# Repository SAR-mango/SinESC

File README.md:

# Current State of the Project
I graduated from UCSB in June 2026, and SinESC has been revived!

After studying electrical engineering for four years, I have realized that the true problem to solve – and the key to SinESC's success – is developing a sensorless FOC algorithm that operates reliably, without manual tuning, across a wide range of motors.

Accordingly, I have shifted away from ST's motor control library in favor of my own software, developed from scratch. For now, I am using evaluation boards to perform testing. Building robust, high-performance hardware is a secondary focus, since this has already been done by others. Nevertheless, I plan to eventually revamp the hardware.

# Overview
SinESC (pronounced "sign ESC," namesake being the sine wave) is an electronic speed controller (ESC) that supports sensorless field-oriented control of three-phase brushless DC motors used by RC drone pilots. For a brief overview of the project and the underlying theory, see [these slides](https://github.com/SAR-mango/SinESC/blob/master/sinesc_slides/sinesc_slides.pdf) – adapted from a presentation I gave at SpaceX for an onsite interview.

The dimensions of the PCBs pictured below are 15x30mm.

# Features, Specifications*
- 90% efficiency (up to 40% longer flight)
- Smooth flight
- Quiet operation
- Bus voltage monitoring for power measurement and under-voltage protection
- Broken-out and labeled debug pins
- 3–6S Li-po battery support
- Maximum 30A continuous, 40A burst current draw

\*Several of the above specifications are currently only theoretical; they have not been confirmed with measurements. This page will be updated immediately when any specification changes or is confirmed.

# Sinusoidal Control: Benefits and a Brief Description
Brushless DC motors work best when their phase voltage waveforms are sinusoid-shaped. Try it yourself—connect a BLDC motor to an oscilloscope and spin the rotor with your fingers. You will see a sine wave. 

Regular BLHELI_32 ESCs use a simple "six-point" motor control method in which the phases are energized to bring the rotor to one of six points on a circle. This method is easy to implement as the rotor position at each point will result in a zero-crossing in the back-EMF from the non-energized phase(s), which is easy to detect. This means that the phase voltage waveforms are trapezoid-shaped rather than sinusoid-shaped. This is not ideal as the fields are not *always* aligned with the rotor to maximize torque. This causes the rotor to effectively "jolt in a circle" rather than spin continuously, resulting in lower efficiency and rougher flight. Furthermore, the sharp edges of the trapezoidal signal also introduce high-frequency noise which contributes to the above disadvantages as well. This also makes the motors run louder and hotter.

Sinusoidal control minimizes torque ripple, maximizing efficiency. The magnetic fields are precisely aligned to exert maximum torque on the rotor at *any* given position and power. Minimized torque ripple leads to smoother flight. Greater efficiency (SinESC achieves > 90% efficiency; trapezoidal ESCs typically achieve around 70%) allows for longer flight times and lower peak currents, which can increase battery longevity as well.

# Current-Sense Topology
Not just any ESC can perform sinusoidal control, and not all sinusoidal ESCs are created equal. Sinusoidal control requires that the ESC know the exact position of the rotor in order to properly align the magnetic field. Perfect alignment results in a perfect sine wave.

There are a few ways to find the position of the rotor:
- The first, most obvious method is to put a hall-effect (or similar) sensor on the motor to determine exactly where the rotor is. This sensor simply feeds data to the ESC. However, this is impractical for drones and wings due to durability, size, and weight concerns.
- The second way is to calculate the position of the rotor based on the currents flowing through each phase. Technically, measuring just the total motor current is sufficient, but this leads to poor position estimation and thus reduced performance. Alternatively, each half-bridge can connect to ground through a series current shunt and the voltage drop across each shunt can be amplified and read by an ADC in a microcontroller. This allows for the current through each phase to be known, resulting in far superior performance. Though more complicated, this is the current-sensing topology that SinESC employs.
- Finally, inline current-sensing is also possible. This technique involves placing shunts in series with only two of the three motor phases, since the third phase current can be calculated with Kirchoff's Current Law. However, this requires complicated, expensive amplifiers as high common-mode rejection ratio is critical. Some gate driver ICs integrate these amplifiers, but their gain and offset cannot be tuned to take full advantage of the ADC resolution. At high currents, ADC resolution is very valuable and should not be wasted. Thus, the second method was selected.

# Hardware Achievements
The 15x30mm SinESC Multi Edition PCB uses 0201-sized components when possible for reduced parasitic influences and reduced size. Maximum component density is approximately 50 components/cm². The microcontroller, gate driver, and current-sense amplifiers (all the control electronics) are implemented on the top layer, leaving the bottom layer for the power electronics. This provides room for wide traces. Multi Edition is designed in KiCAD and adheres to OSHPark design rules. All additional libraries are within the project files.

SinESC is designed specifically for efficiency and robustness:
- ST Microelectronics STM32F303C(Bx/Cx) microcontroller
- Maxim Integrated MAX4239 precision op-amps for current-sensing. Incredibly low input offset voltage of 0.1µV. Gain = 30V/V; offset tuned to use the full ADC resolution.
- Low-resistance current shunts (1mΩ) for reduced power loss
- Switching regulator provides logic-level voltage supply for control electronics (efficiency > 80%)
- Thermally optimized PCB layout
- Trinamic Motion Control TMC6100-LA gate driver
  - Fast switching slopes achieved with high gate drive current of 1.5A, decreasing switching losses
- Infineon Technologies BSC010N04LSI N-channel MOSFETs
  - Extremely low on-resistance (Rdson = 1.05mΩ) for reduced power loss
  - High drain-source voltage (Vds = 40V) for immunity to voltage spikes even at 6S Li-po voltages
- High-quality passive components
  - TDK ceramic capacitors
  - Panasonic metal film resistors (all 1% tolerance including shunts)

\*Many of these specifications will change; see the top of this page

# Versions
Regular Semantic Versioning is used for all software components of the project. As for PCB designs, Semantic Versioning has been modified. After Multi v2.3C, versions only reflect the PCB design since schematic changes directly influence the PCB. They are written like so:

vX.YZ where X and Y are numbers and Z is a letter. "v" is sometimes omitted.
- If a minor change is made that does NOT require a new stencil OR an updated BOM, Z is incremented.
- If a minor change requires a new stencil and/or an updated BOM, Y is incremented and Z is reset. Ideally, few minor changes are made between major releases.
- If a major change is made, X is incremented and Y and Z are reset.

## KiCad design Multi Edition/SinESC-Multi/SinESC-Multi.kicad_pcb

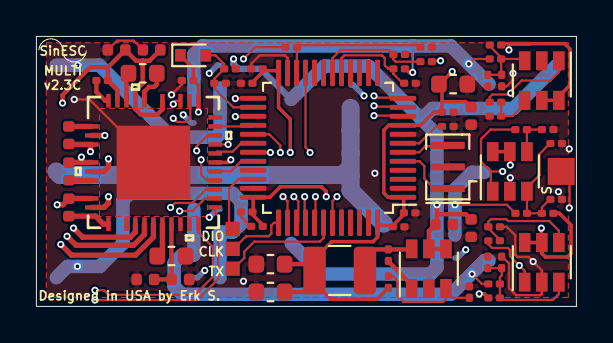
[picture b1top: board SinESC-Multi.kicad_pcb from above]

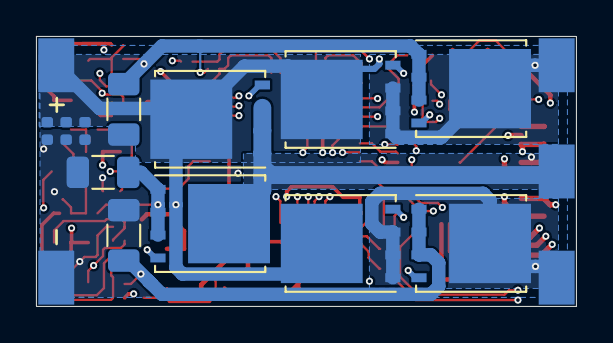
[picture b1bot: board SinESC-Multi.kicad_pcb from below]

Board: 4 copper layers, 30.0 x 15.0 mm, 84 parts (17 on the bottom side), 58 nets.

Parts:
C1, C2, C4, C8, C20, C23, C30: 100nF; C_0201_0603Metric
C3, C5, C6, C7, C9, C10, C12, C14, C15, C19: 6.8nF; C_0201_0603Metric
C11, C16, C17, C18, C21, C22, C26, C28, C29, C31, C32, C33: 1µF; C_0402_1005Metric
C13, C25, C34, C35: 10µF; C_0603_1608Metric
C24: 22nF; C_0603_1608Metric
C27: 100nF; C_0402_1005Metric
D1: BAT30KFILM; D_SOD-523
J1, J2, J3, J4, J5: Pad_3x2mm
J6: Pad_1.5mm_Square
L1: 10µH; L_1210_3225Metric
Q1, Q2, Q3, Q4, Q5, Q6: BSC010N04LSI; TDSON-8-1
R1, R10, R19: 86.6Ω; R_0201_0603Metric
R2, R6, R11: 1.5kΩ; R_0201_0603Metric
R3, R7, R12: 1mΩ; R_1206_3216Metric
R4, R13, R20: 5.1kΩ; R_0201_0603Metric
R5, R14, R21: 976Ω; R_0201_0603Metric
R8, R16, R17, R22: 15kΩ; R_0201_0603Metric
R9, R18, R23: 470Ω; R_0201_0603Metric
R15, R25: 120kΩ; R_0201_0603Metric
R24: 52.3kΩ; R_0201_0603Metric
TP1, TP2, TP3: Pad_0.8mm_Square
U1: STM32F303CBT7; LQFP-48_7x7mm_P0.5mm
U2, U3, U5: MAX4239AUT; SOT-23-6
U4: TMC6100-LA
U6: TPS560430XDBVR; SOT-23-6
Y1: 8MHz; Resonator_SMD_muRata_CSTxExxV-3Pin_3.0x1.1mm

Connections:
+3V3: C1.1, C3.1, C4.1, C5.1, C8.1, C9.1, C10.1, C11.1, C13.1, C20.1, C34.2, C35.2, D1.1, L1.2, R4.1, R13.1, R20.1, R25.2, U1.1, U1.9, U1.24, U1.36, U1.48, U2.5, U2.6, U3.5, U3.6, U4.16, U4.22, U5.5, U5.6
+5V: C21.1, C22.1, U4.7
+12V: C25.1, U4.6
CU: C16.2, U4.1
CUR_U: R8.1, U1.10, U2.1
CUR_V: R17.1, U1.11, U3.1
CUR_W: R22.1, U1.12, U5.1
CV: C17.2, U4.35
CW: C18.2, U4.30
DRV_EN: U1.21, U4.24
DRV_FAULT: U1.25, U4.23
Earth: C1.2, C2.2, C3.2, C4.2, C5.2, C6.1, C7.2, C8.2, C9.2, C10.2, C11.2, C12.1, C13.2, C14.2, C15.1, C19.2, C20.2, C21.2, C22.2, C25.2, C26.2, C27.2, C28.2, C29.2, C31.2, C32.2, C33.2, C34.1, C35.1, J5.1, R3.1, R5.2, R7.1, R9.2, R12.1, R14.2, R16.2, R18.2, R21.2, R23.2, R24.2, U1.8, U1.23, U1.35, U1.44, U1.47, U2.2, U3.2, U4.8, U4.21, U4.38, U5.2, U6.2, Y1.2
HSU: Q1.4, U4.37
HSV: Q3.4, U4.34
HSW: Q5.4, U4.31
LSU: Q2.4, U4.5
LSV: Q4.4, U4.4
LSW: Q6.4, U4.3
unnamed: C2.1, U1.7
unnamed: C7.1, R1.1, R4.2, R5.1, U2.3
unnamed: C14.1, R10.1, R13.2, R14.1, U3.3
unnamed: C19.1, R19.1, R20.2, R21.1, U5.3
unnamed: C23.2, U4.29
unnamed: C24.1, U4.26
unnamed: C24.2, U4.27
unnamed: C30.1, L1.1, U6.6
unnamed: C30.2, U6.1
unnamed: R8.2, R9.1, U2.4
unnamed: R17.2, R18.1, U3.4
unnamed: R22.2, R23.1, U5.4
unnamed: R24.1, R25.1, U6.3
unnamed: U1.5, Y1.1
unnamed: U1.6, Y1.3
OCP_COMP_U: C6.2, R2.1, U1.17
OCP_COMP_V: C12.2, R6.1, U1.18
OCP_COMP_W: C15.2, R11.1, U1.22
PWM_U_H: U1.29, U4.14
PWM_U_L: U1.32, U4.15
PWM_V_H: U1.30, U4.17
PWM_V_L: U1.27, U4.18
PWM_W_H: U1.31, U4.19
PWM_W_L: U1.28, U4.20
SHUNT_U: Q2.1, Q2.2, Q2.3, R1.2, R2.2, R3.2
SHUNT_V: Q4.1, Q4.2, Q4.3, R6.2, R7.2, R10.2
SHUNT_W: Q6.1, Q6.2, Q6.3, R11.2, R12.2, R19.2
SINWIRE: J6.1, U1.43
SPI_CSN: U1.38, U4.10
SPI_SCK: U1.39, U4.11
SPI_SDI: U1.41, U4.12
SPI_SDO: U1.40, U4.13
SWCLK: TP2.1, U1.37
SWDIO: TP1.1, U1.34
U: C16.1, J1.1, Q1.1, Q1.2, Q1.3, Q2.5, U4.36
UART_TX: TP3.1, U1.42
V: C17.1, J2.1, Q3.1, Q3.2, Q3.3, Q4.5, U4.33
VBUS: C23.1, C26.1, C27.1, C28.1, C29.1, C31.1, C32.1, C33.1, J4.1, Q1.5, Q3.5, Q5.5, R15.1, U4.25, U4.28, U6.4, U6.5
VBUS_SENSE: D1.2, R15.2, R16.1, U1.26
W: C18.1, J3.1, Q5.1, Q5.2, Q5.3, Q6.5, U4.32

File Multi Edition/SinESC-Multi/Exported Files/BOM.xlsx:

| SinESC Multi v2.3C - Bill of Materials (BOM) |  | Line Item | Qty | Reference(s) | Value | Manufacturer Part #
 | Source: SinESC\Multi Edition\SinESC-Multi\SinESC-Multi.sch |  | 1 | 7 | C1, C2, C4, C8, C20, C23, C30 | 100nF | C0603X5R1E104K030BB
 | Generated on: 12/30/2020 |  | 2 | 10 | C3, C5, C6, C7, C9, C10, C12, C14, C15, C19 | 6.8nF | GRM033R71E682KE14D
 | Tool: Eeschema (5.1.6)-1 |  | 3 | 12 | C11, C16, C17, C18, C21, C22, C26, C28, C29, C31, C32, C33 | 1µF | UMK105CBJ105MV-F
 | Generator: bom_csv_grouped_by_value.py |  | 4 | 4 | C13, C25, C34, C35 | 10µF | C1608X5R1E106M080AC
 | Total Component Count: 75 |  | 5 | 1 | C24 | 22nF | C1608X7R2A223K080AA
 | Unique Component Count: 23 |  | 6 | 1 | C27 | 100nF | C1005X7R1H104K050BB
 | BOM Consolidation Ratio (Total/Unique): 3.261 |  | 7 | 1 | D1 | BAT30KFILM | BAT30KFILM
 |  |  | 8 | 1 | L1 | 10µH | CBC3225T100KR
 |  |  | 9 | 6 | Q1, Q2, Q3, Q4, Q5, Q6 | BSC010N04LSI | BSC010N04LSIATMA1
 |  |  | 10 | 3 | R1, R10, R19 | 86.6Ω | ERJ-1GNF86R6C
 |  |  | 11 | 3 | R2, R6, R11 | 1.5kΩ | ERJ-1GNF1501C
 |  |  | 12 | 3 | R3, R7, R12 | 1mΩ | CSR1206-0R001F1
 |  |  | 13 | 3 | R4, R13, R20 | 5.1kΩ | ERJ-1GNF5101C
 |  |  | 14 | 3 | R5, R14, R21 | 976Ω | ERJ-1GNF9760C
 |  |  | 15 | 4 | R8, R16, R17, R22 | 15kΩ | ERJ-1GNF1502C
 |  |  | 16 | 3 | R9, R18, R23 | 470Ω | ERJ-1GNF4700C
 |  |  | 17 | 2 | R15, R25 | 120kΩ | ERJ-1GNF1203C
 |  |  | 18 | 1 | R24 | 52.3kΩ | ERJ-1GNF5232C
 |  |  | 19 | 1 | U1 | STM32F303CBT7 | STM32F303CBT7
 |  |  | 20 | 3 | U2, U3, U5 | MAX4239AUT | MAX4239AUT+T
 |  |  | 21 | 1 | U4 | TMC6100-LA | TMC6100-LA-T
 |  |  | 22 | 1 | U6 | TPS560430XDBVR | TPS560430XDBVR
 |  |  | 23 | 1 | Y1 | 8MHz | CSTNE8M00G550000R0

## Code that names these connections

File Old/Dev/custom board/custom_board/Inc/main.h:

/* USER CODE BEGIN Header */
/**
  ******************************************************************************
  * @file           : main.h
  * @brief          : Header for main.c file.
  *                   This file contains the common defines of the application.
  ******************************************************************************
  * @attention
  *
  * <h2><center>&copy; Copyright (c) 2021 STMicroelectronics.
  * All rights reserved.</center></h2>
  *
  * This software component is licensed by ST under Ultimate Liberty license
  * SLA0044, the "License"; You may not use this file except in compliance with
  * the License. You may obtain a copy of the License at:
  *                             www.st.com/SLA0044
  *
  ******************************************************************************
  */
/* USER CODE END Header */

/* Define to prevent recursive inclusion -------------------------------------*/
#ifndef __MAIN_H
#define __MAIN_H

#ifdef __cplusplus
extern "C" {
#endif

/* Includes ------------------------------------------------------------------*/
#include "stm32f3xx_hal.h"

/* Private includes ----------------------------------------------------------*/
/* USER CODE BEGIN Includes */

/* USER CODE END Includes */

/* Exported types ------------------------------------------------------------*/
/* USER CODE BEGIN ET */

/* USER CODE END ET */

/* Exported constants --------------------------------------------------------*/
/* USER CODE BEGIN EC */

/* USER CODE END EC */

/* Exported macro ------------------------------------------------------------*/
/* USER CODE BEGIN EM */

/* USER CODE END EM */

void HAL_TIM_MspPostInit(TIM_HandleTypeDef *htim);

/* Exported functions prototypes ---------------------------------------------*/
void Error_Handler(void);

/* USER CODE BEGIN EFP */

/* USER CODE END EFP */

/* Private defines -----------------------------------------------------------*/
#define M1_CURR_AMPL_U_Pin GPIO_PIN_0
#define M1_CURR_AMPL_U_GPIO_Port GPIOA
#define M1_CURR_AMPL_V_Pin GPIO_PIN_1
#define M1_CURR_AMPL_V_GPIO_Port GPIOA
#define M1_CURR_AMPL_W_Pin GPIO_PIN_2
#define M1_CURR_AMPL_W_GPIO_Port GPIOA
#define DRV_EN_Pin GPIO_PIN_10
#define DRV_EN_GPIO_Port GPIOB
#define DRV_FAULT_Pin GPIO_PIN_12
#define DRV_FAULT_GPIO_Port GPIOB
#define M1_PWM_VL_Pin GPIO_PIN_14
#define M1_PWM_VL_GPIO_Port GPIOB
#define M1_PWM_WL_Pin GPIO_PIN_15
#define M1_PWM_WL_GPIO_Port GPIOB
#define M1_PWM_UH_Pin GPIO_PIN_8
#define M1_PWM_UH_GPIO_Port GPIOA
#define M1_PWM_VH_Pin GPIO_PIN_9
#define M1_PWM_VH_GPIO_Port GPIOA
#define M1_PWM_WH_Pin GPIO_PIN_10
#define M1_PWM_WH_GPIO_Port GPIOA
#define M1_PWM_UL_Pin GPIO_PIN_11
#define M1_PWM_UL_GPIO_Port GPIOA
#define SPI1_NSS_SOFT_Pin GPIO_PIN_15
#define SPI1_NSS_SOFT_GPIO_Port GPIOA
#define UART_TX_Pin GPIO_PIN_6
#define UART_TX_GPIO_Port GPIOB
#define UART_RX_Pin GPIO_PIN_7
#define UART_RX_GPIO_Port GPIOB
/* USER CODE BEGIN Private defines */

/* USER CODE END Private defines */

#ifdef __cplusplus
}
#endif

#endif /* __MAIN_H */

/************************ (C) COPYRIGHT STMicroelectronics *****END OF FILE****/

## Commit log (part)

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2020-09-03 Revert "Update README.md"
    This reverts commit 9b0668ebfc45d7c626aa47909acdf1ce1732b061.
2020-09-03 Added remaining files
2020-09-03 Add 3D model of TMC6100
2020-09-03 Add custom libraries and 3D renders
2020-09-03 PCB trace conditioning
2020-09-03 Update version numbering and 3D renders
2020-09-03 Update 3D renders
2020-09-03 Change TMC6100 attribute from through-hole to SMD
2020-09-03 Update BOM
2020-09-06 Add logo to schematic
2020-09-10 Update logo
2020-09-10 Add new logo to schematic
2020-09-10 Update schematic cosmetics
2020-09-17 Update R24 footprint & 3D model
2020-09-18 Remove 3D renders
2020-09-23 Change resonator to part with interchangeable pins
2020-09-24 Change total component count to correct value of 75, recalculate BOM Consolidation Ratio
2020-10-01 Add plain gerber files in addition to zipped gerber files
2020-10-09 Update solder paste settings for improved yield (when assembled with stencil)
2020-10-09 Temporarily remove Wing Edition files
2020-10-09 Add Wing Edition files
2020-10-09 Temporarily remove Development folder
2020-10-09 Add Dev materials
2020-10-15 Update assembly references
2020-12-27 Rename all project files to stop reflecting board version
2020-12-28 Fix issue in the schematic in which the buck converter's 3.3V output is not connected to the rest of the 3.3V rail
2020-12-28 Implement critical fix according to updated schematic, several other small updates (layout & silkscreen conditioning)
2020-12-28 Modify all exported files to reflect PCB changes
2020-12-29 Change via drill diameter to 0.2mm from 0.254mm. This allows the design to take full advantage of PCBWay's capabilities, while it remains compatible with OSH Park's minimum design rules as well (as t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
2020-12-29 Remove gerber files. It is best to generate these manually when necessary.
2020-12-30 Decrease STM32 LQFP48 pad size from 0.3mm to 0.28mm so more manufacturers support solder mask between the pads
2020-12-30 Update date reflected on sheet. Remove "Made in USA" from silkscreen to avoid customs issues when ordering boards from outside the U.S.
2020-12-30 Update "Source" field in BOM to reflect latest file name and path
2020-12-31 Fix another issue in which the bootstrap capacitors were not connected to the source pins of the high-side FETs
2021-01-10 Ignore "fp-info-cache" KiCAD file
2021-01-10 Reorganize all development files; ensure all necessary documentation is present
2021-01-18 Add packages/footprints to BOM
2021-01-22 Add several useful STM32 docs
2021-01-25 Remove '/' from datasheet filenames; this was causing issues on Windows
2021-01-25 Multiple changes to SPI code and TMC6100 config
2021-06-30 Reorganized/moved old files, added additional red-only and black-only logos
2023-07-05 Add license
2024-05-09 remove text from render
2025-10-30 remove old stuff and add slides
2025-10-30 add link to slides in readme
2025-10-30 fix link format
2025-11-11 wording
    Updated the link text in the README for clarity.

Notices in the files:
Multi Edition/SinESC-Multi/SinESC-Multi.kicad_pcb:
Drawn by Erk S., © 2020 SinESC
parts and their libraries:
Copyright 2016 Accelerated Designs. All rights reserved.
